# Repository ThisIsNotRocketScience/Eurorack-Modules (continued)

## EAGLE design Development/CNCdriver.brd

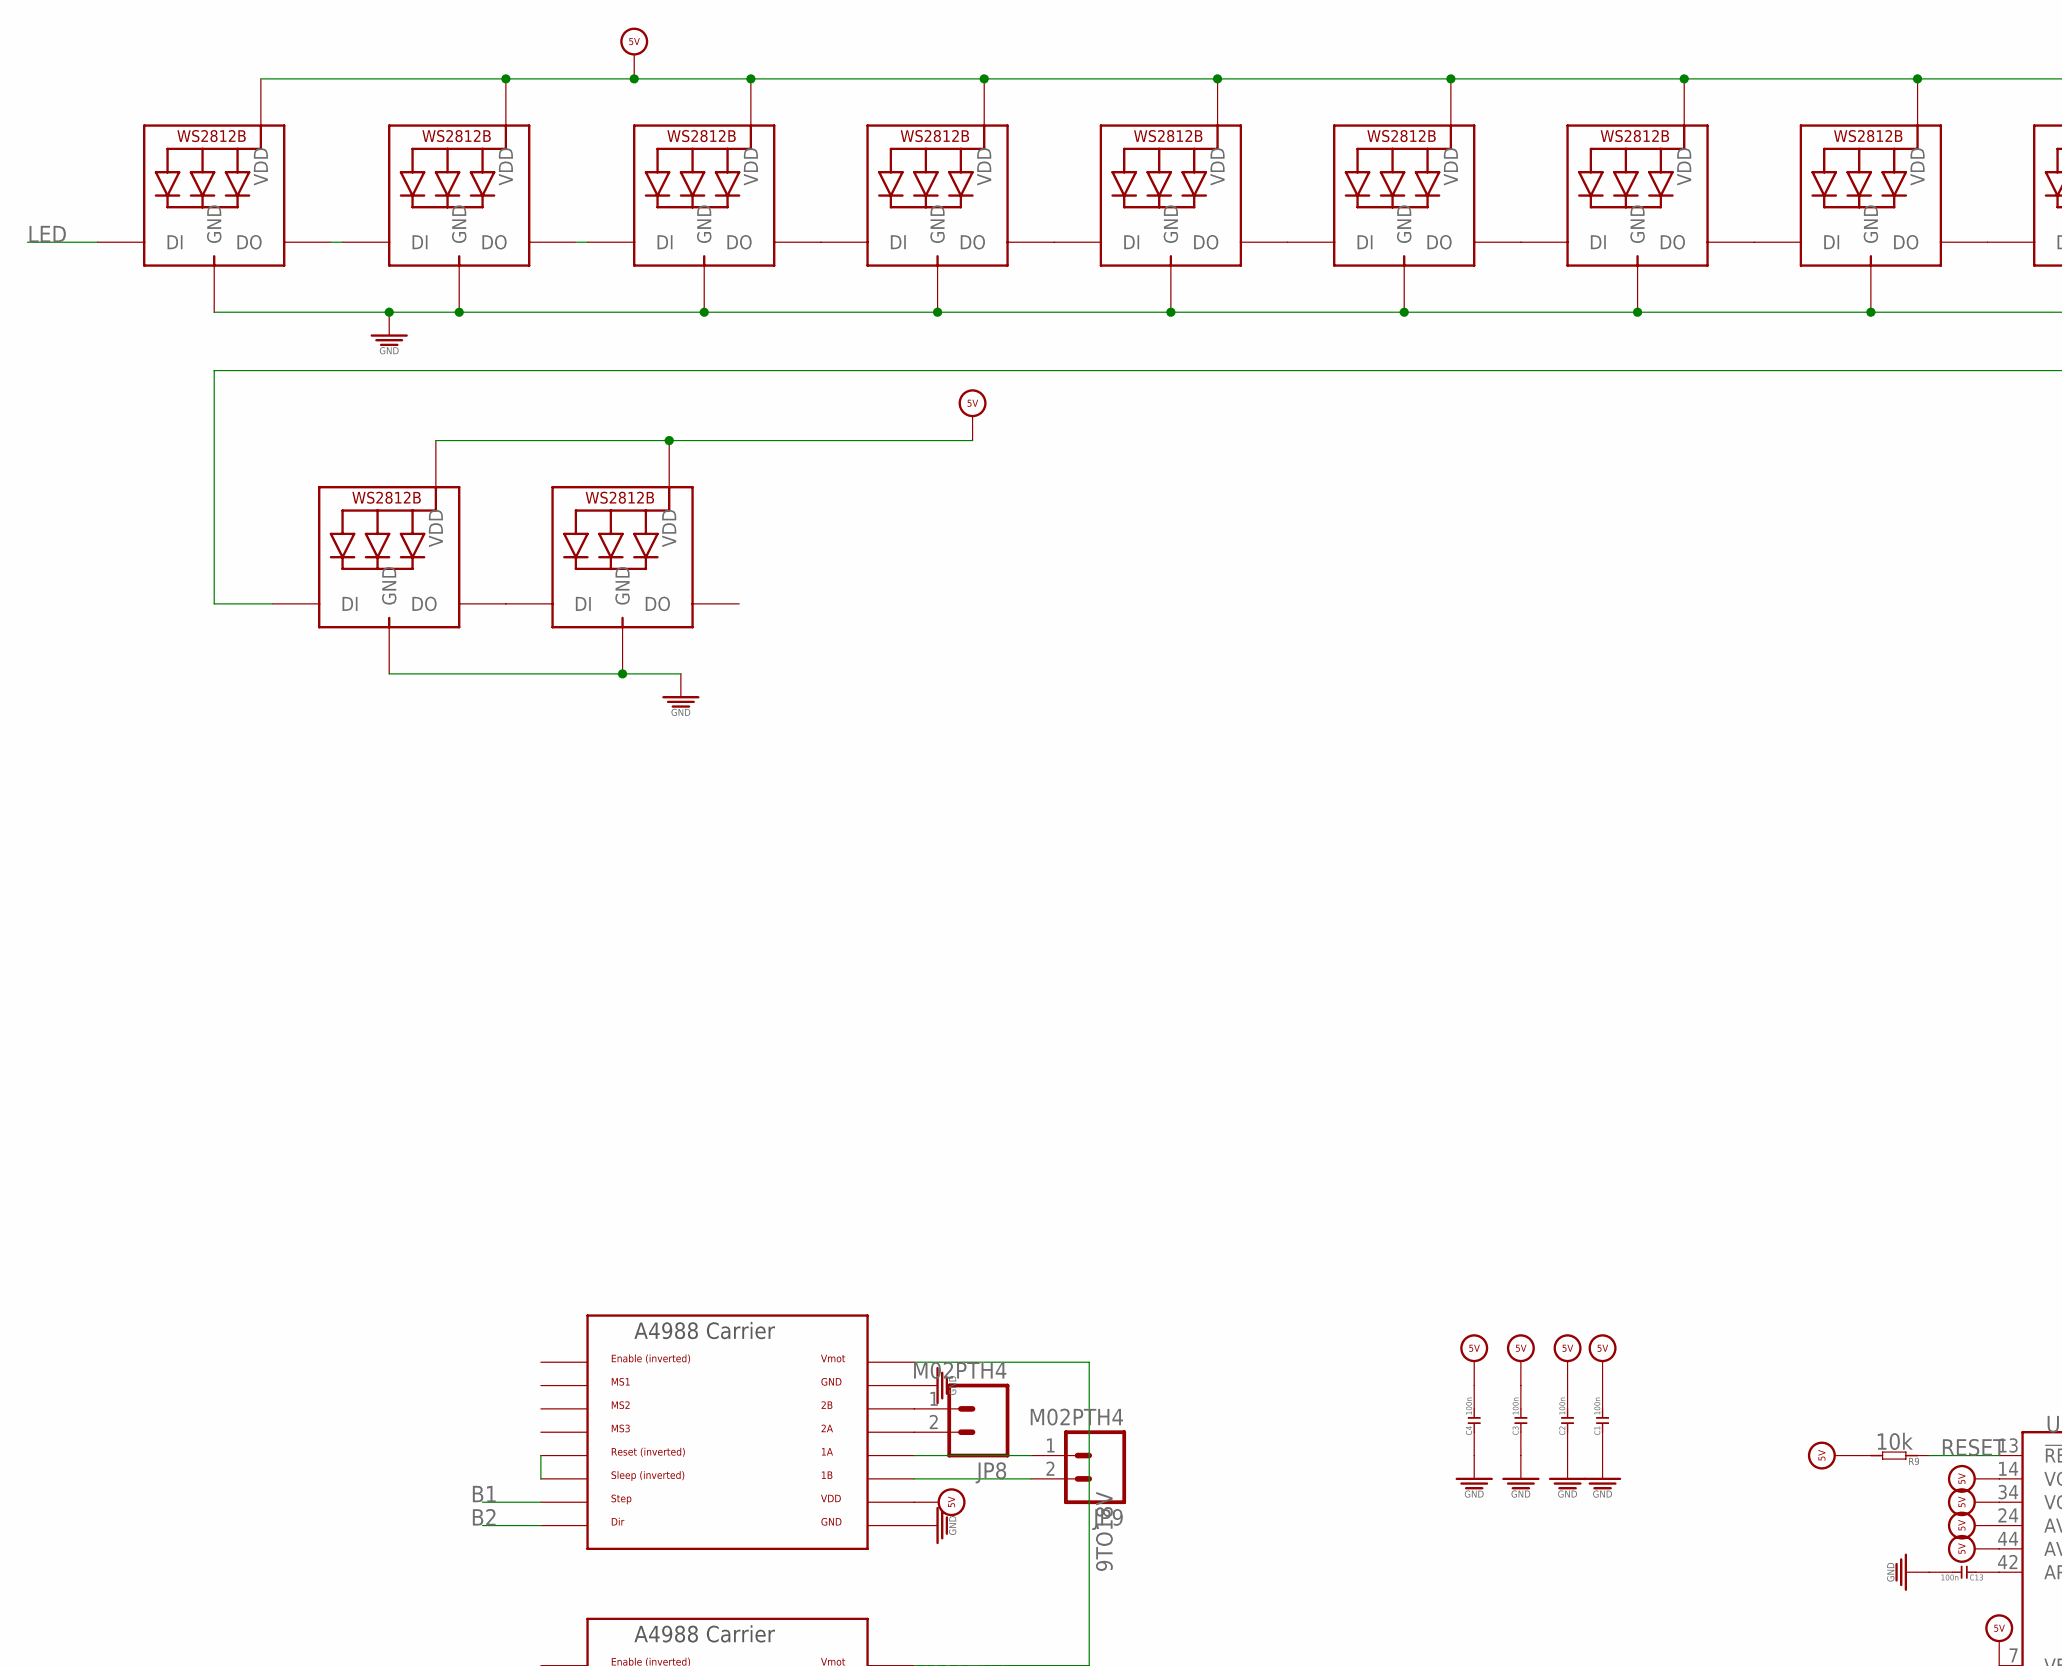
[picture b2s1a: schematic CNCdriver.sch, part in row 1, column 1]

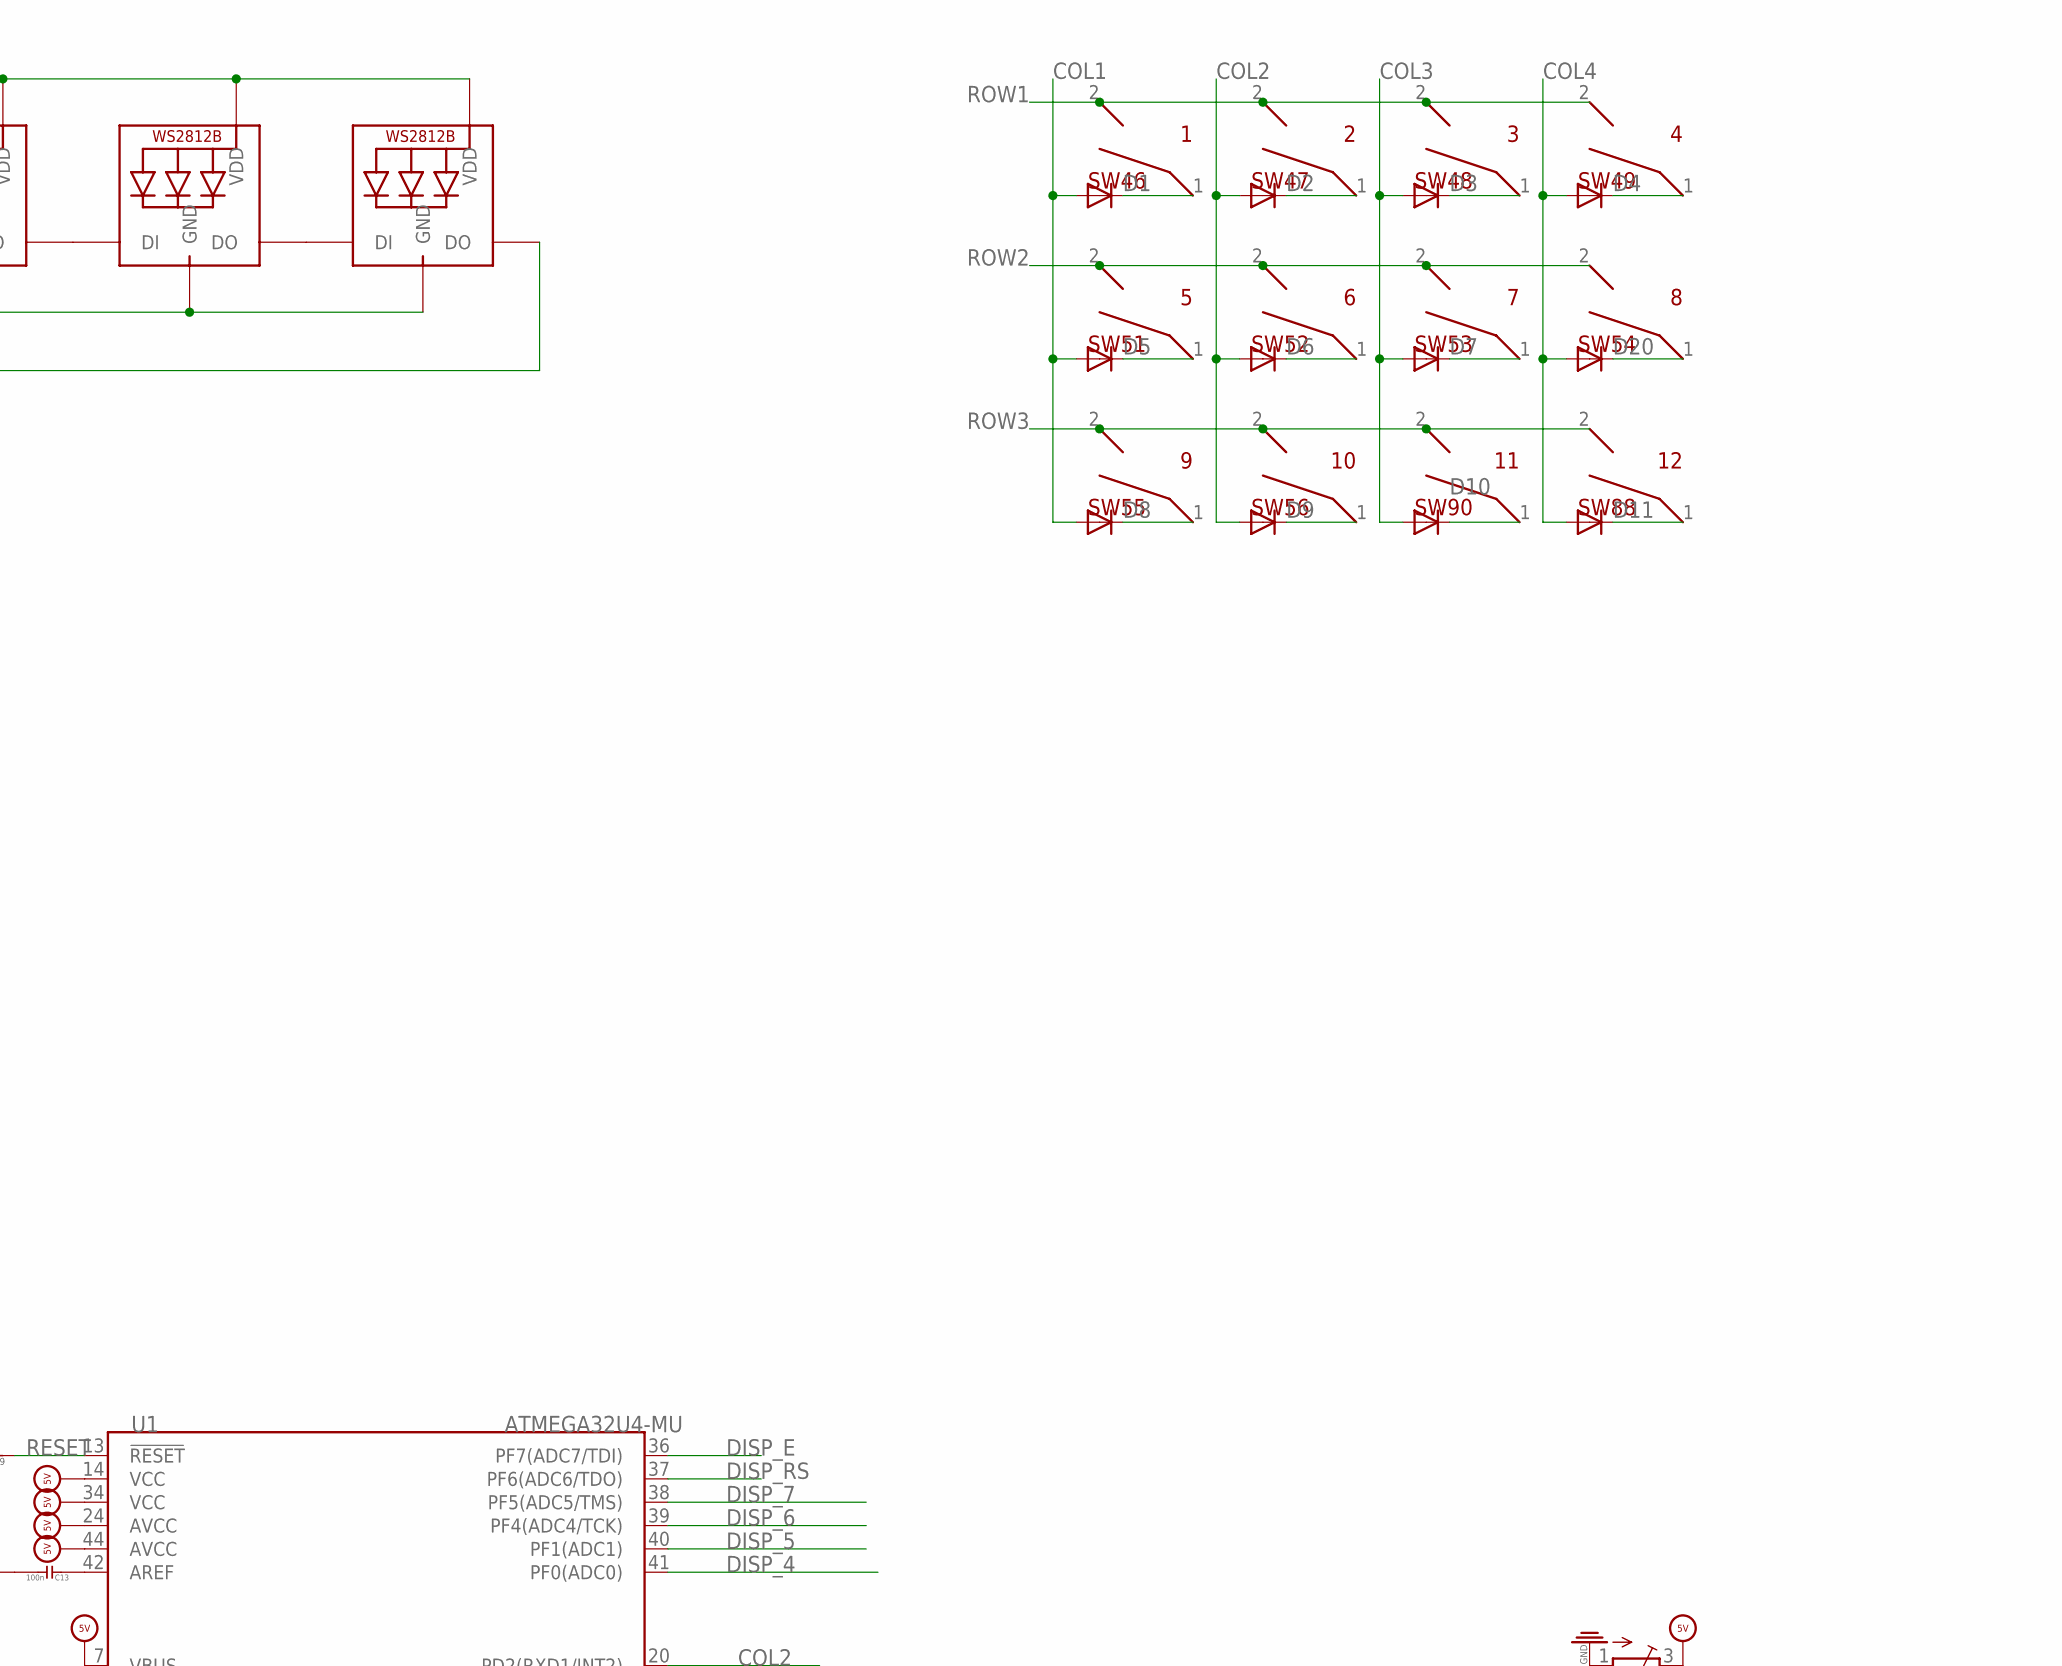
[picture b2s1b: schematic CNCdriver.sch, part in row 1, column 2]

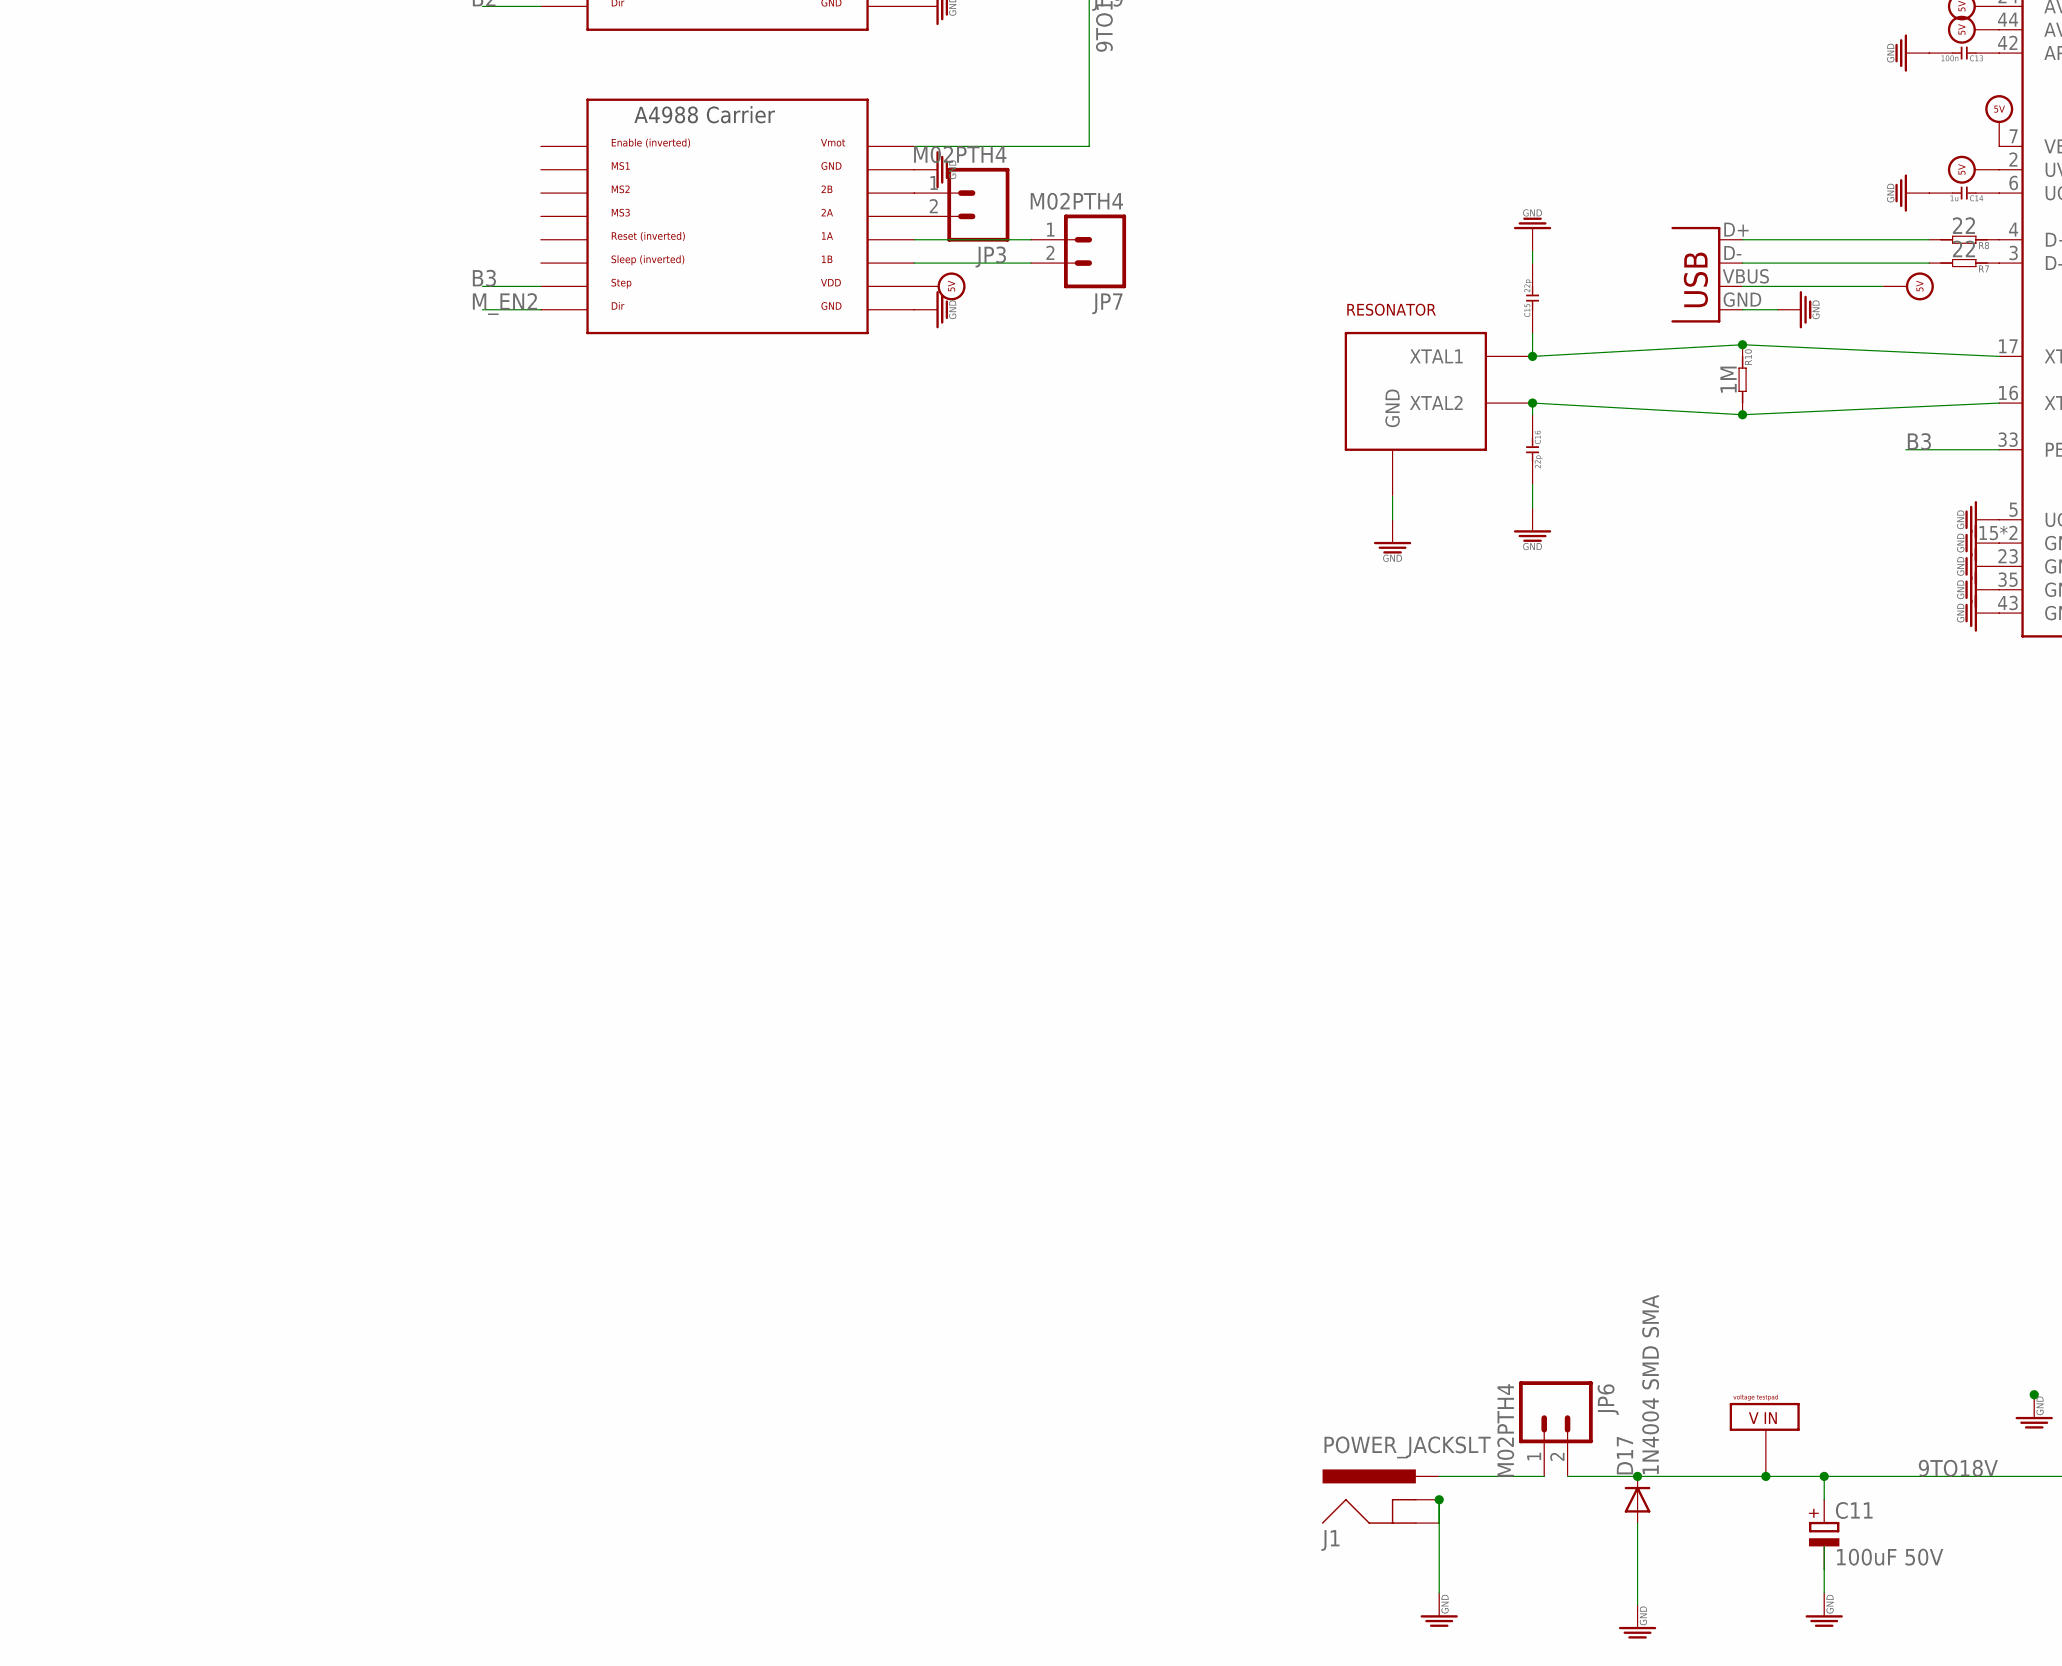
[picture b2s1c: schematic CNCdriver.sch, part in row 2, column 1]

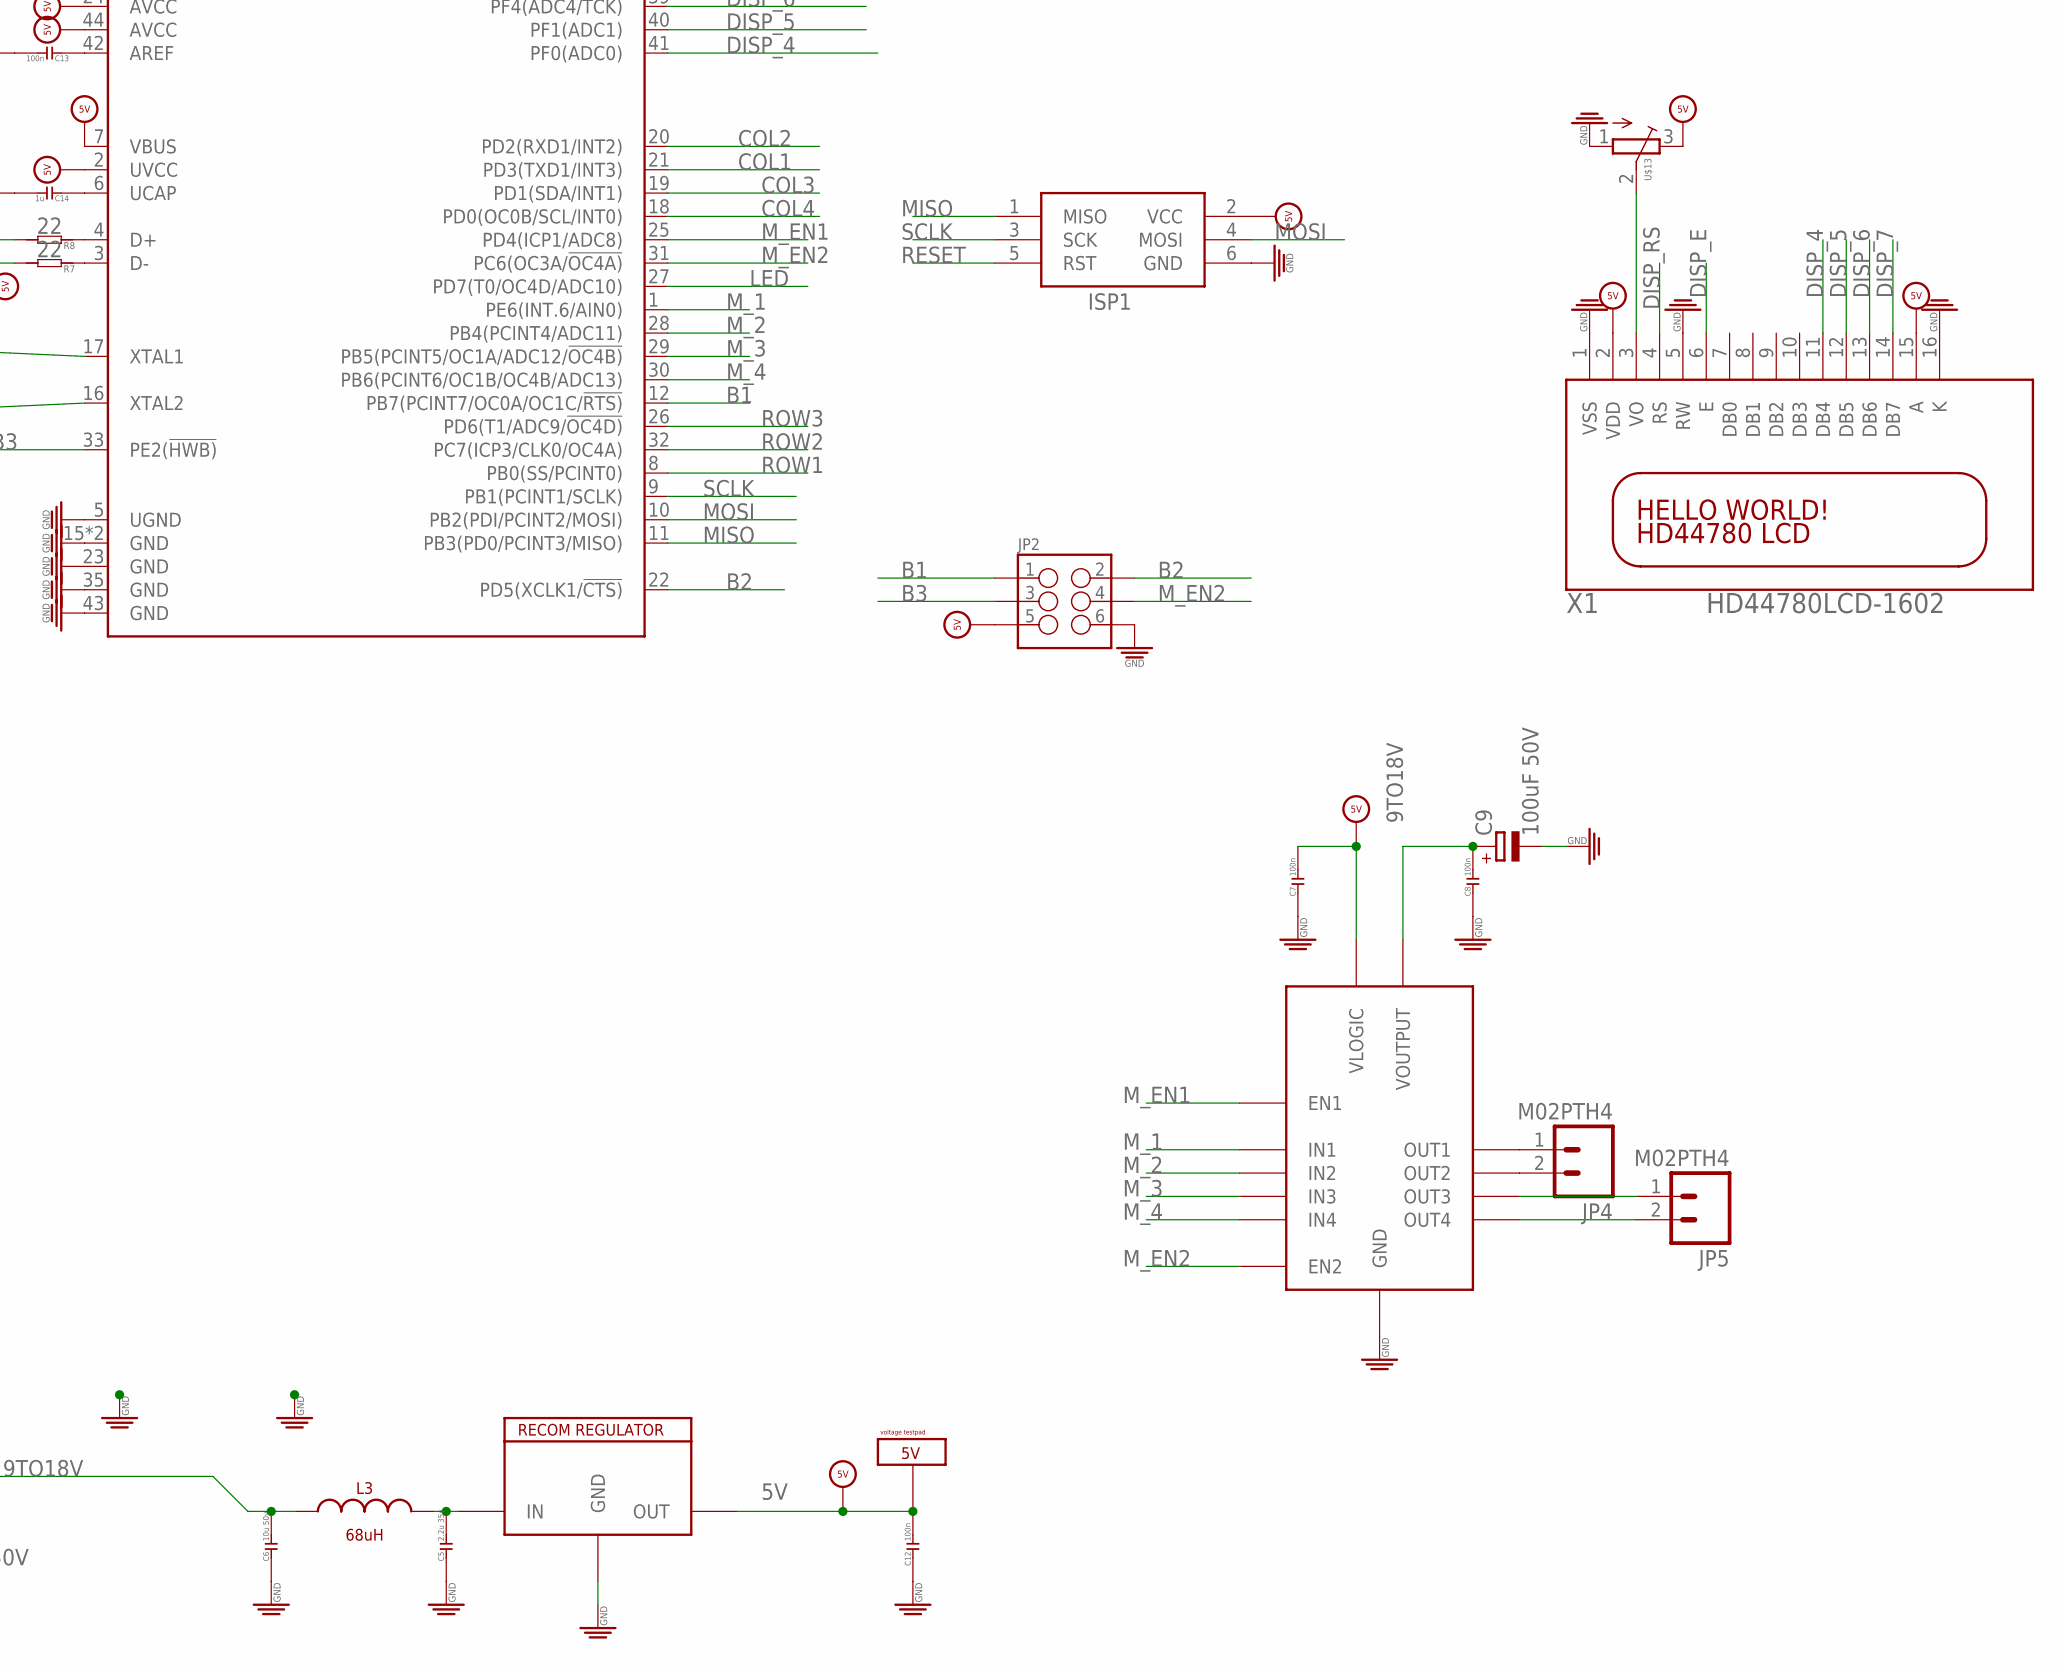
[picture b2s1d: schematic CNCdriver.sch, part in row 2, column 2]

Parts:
C1, C2, C3, C4, C7, C8, C12, C13: 100n; C0603
C5: 2.2u 35v; C0603
C6: 10u 50v; C0603
C9, C11: 100uF 50V; 153CLV-1010
C14: 1u; C0603
C15, C16: 22p; C0603
D1, D2, D3, D4, D5, D6, D7, D8, D9, D10, D11, D20: CGRM4001-G; SOD-123_MINI-SMA
D17: 1N4004 SMD SMA; DO214AC
ISP1: AVRISP-6; AVRISP
J1: POWER_JACKSLT; POWER_JACK_SLOT
JP1: USB-B; USB-B-PTH
JP2: M03X2; 2X3-SHROUDED
JP3, JP4, JP5, JP6, JP7, JP8, JP9: M02PTH4; 1X02_XTRA_BIG
L3: 68uH; SWRB120XS
LED13, LED14, LED15, LED16, LED17, LED18, LED19, LED20, LED21, LED22, LED23, LED24: WS2812B3535; LED3535
R7, R8: 22; R0603
R9: 10k; R0603
R10: 1M; R0603
SW46: 1; MX1A-XXNW
SW47: 2; MX1A-XXNW
SW48: 3; MX1A-XXNW
SW49: 4; MX1A-XXNW
SW51: 5; MX1A-XXNW
SW52: 6; MX1A-XXNW
SW53: 7; MX1A-XXNW
SW54: 8; MX1A-XXNW
SW55: 9; MX1A-XXNW
SW56: 10; MX1A-XXNW
SW88: 12; MX1A-XXNW
SW90: 11; MX1A-XXNW
U1: ATMEGA32U4-MU; QFN44
U$9: L293D; SO20
U$13: TRIMPOTTC33X; TC33X
U$15, U$16: A4983CARRIER; A4988BREAKOUT
U$17: RECOM_REGULATOR; R-78E5.0-1.0
U$25, U$29: VOLTAGETESTPAD; POWERTESTPAD
U$60: RESONATOR; 16MHZXTAL
X1: HD44780LCD-1602; LCD1602

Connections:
9TO18V: C6.2, C8.2, C9.+, C11.+, D17.C, JP6.2, L3.P$1, U$9.P$10 (VOUTPUT), U$15.VMOT, U$16.VMOT, U$29.P$1, U$29.P$2, U$29.P$3
B1: JP2.1, U1.12 (PB7(PCINT7/OC0A/OC1C/!RTS)), U$15.STEP
B2: JP2.2, U1.22 (PD5(XCLK1/!CTS)), U$15.DIR
B3: JP2.3, U1.33 (PE2(!HWB)), U$16.STEP
COL1: D1.A, D5.A, D8.A, U1.21 (PD3(TXD1/INT3))
COL2: D2.A, D6.A, D9.A, U1.20 (PD2(RXD1/INT2))
COL3: D3.A, D7.A, D10.A, U1.19 (PD1(SDA/INT1))
COL4: D4.A, D11.A, D20.A, U1.18 (PD0(OC0B/SCL/INT0))
DISP_4: U1.41 (PF0(ADC0)), X1.11 (DB4)
DISP_5: U1.40 (PF1(ADC1)), X1.12 (DB5)
DISP_6: U1.39 (PF4(ADC4/TCK)), X1.13 (DB6)
DISP_7: U1.38 (PF5(ADC5/TMS)), X1.14 (DB7)
DISP_E: U1.36 (PF7(ADC7/TDI)), X1.6 (E)
DISP_RS: U1.37 (PF6(ADC6/TDO)), X1.4 (RS)
GND: C1.1, C2.1, C3.1, C4.1, C5.1, C6.1, C7.1, C8.1, C9.-, C11.-, C12.1, C13.2, C14.2, C15.2, C16.2, D17.A, ISP1.6 (GND), J1.GND@1 (GNDBREAK), J1.GND@2 (GND), JP1.GND, JP2.6, LED13.3 (GND), LED14.3 (GND), LED15.3 (GND), LED16.3 (GND), LED17.3 (GND), LED18.3 (GND), LED19.3 (GND), LED20.3 (GND), LED21.3 (GND), LED22.3 (GND), LED23.3 (GND), LED24.3 (GND), U1.5 (UGND), U1.15 (GND), U1.23 (GND), U1.35 (GND), U1.43 (GND), U1.TAB (GND), U$9.P$4 (GND), U$9.P$5 (GND), U$9.P$6 (GND), U$9.P$7 (GND), U$9.P$14 (GND), U$9.P$15 (GND), U$9.P$16 (GND), U$9.P$17 (GND), U$13.1 (A), U$15.GND, U$15.GND@0 (GND), U$16.GND, U$16.GND@0 (GND), U$17.P$2 (GND), U$60.P$2 (GND), U$60.P$4 (GND), X1.1 (VSS), X1.5 (RW), X1.16 (K)
LED: LED13.4 (DI), U1.27 (PD7(T0/OC4D/ADC10))
MISO: ISP1.1 (MISO), U1.11 (PB3(PD0/PCINT3/MISO))
MOSI: ISP1.4 (MOSI), U1.10 (PB2(PDI/PCINT2/MOSI))
M_1: U1.1 (PE6(INT.6/AIN0)), U$9.P$2 (IN1)
M_2: U1.28 (PB4(PCINT4/ADC11)), U$9.P$9 (IN2)
M_3: U1.29 (PB5(PCINT5/OC1A/ADC12/!OC4B)), U$9.P$12 (IN3)
M_4: U1.30 (PB6(PCINT6/OC1B/OC4B/ADC13)), U$9.P$19 (IN4)
M_EN1: U1.25 (PD4(ICP1/ADC8)), U$9.P$1 (EN1)
M_EN2: JP2.4, U1.31 (PC6(OC3A/!OC4A)), U$9.P$11 (EN2), U$16.DIR
unnamed: D1.C, SW46.1
unnamed: D2.C, SW47.1
unnamed: D3.C, SW48.1
unnamed: D4.C, SW49.1
unnamed: D5.C, SW51.1
unnamed: D6.C, SW52.1
unnamed: D7.C, SW53.1
unnamed: D8.C, SW55.1
unnamed: D9.C, SW56.1
unnamed: D10.C, SW90.1
unnamed: D11.C, SW88.1
unnamed: U$15.RST, U$15.SLP (SLEEP)
unnamed: JP7.1, U$16.1A
unnamed: JP7.2, U$16.1B
unnamed: JP3.2, U$16.2A
unnamed: JP3.1, U$16.2B
unnamed: JP9.1, U$15.1A
unnamed: JP9.2, U$15.1B
unnamed: JP8.2, U$15.2A
unnamed: D20.C, SW54.1
unnamed: J1.PWR, JP6.1
unnamed: C5.2, L3.P$2, U$17.P$1 (IN)
unnamed: JP8.1, U$15.2B
unnamed: U$13.2 (S), X1.3 (VO)
unnamed: JP4.1, U$9.P$3 (OUT1)
unnamed: JP4.2, U$9.P$8 (OUT2)
unnamed: JP5.1, U$9.P$13 (OUT3)
unnamed: JP5.2, U$9.P$18 (OUT4)
unnamed: LED13.2 (DO), LED14.4 (DI)
unnamed: LED14.2 (DO), LED15.4 (DI)
unnamed: LED15.2 (DO), LED16.4 (DI)
unnamed: LED16.2 (DO), LED17.4 (DI)
unnamed: LED18.2 (DO), LED19.4 (DI)
unnamed: LED19.2 (DO), LED20.4 (DI)
unnamed: LED20.2 (DO), LED21.4 (DI)
unnamed: LED21.2 (DO), LED22.4 (DI)
unnamed: LED17.2 (DO), LED18.4 (DI)
unnamed: LED23.2 (DO), LED24.4 (DI)
unnamed: LED22.2 (DO), LED23.4 (DI)
unnamed: JP1.D-, R7.2
unnamed: JP1.D+, R8.2
unnamed: C13.1, U1.42 (AREF)
unnamed: R8.1, U1.4 (D+)
unnamed: R7.1, U1.3 (D-)
unnamed: C14.1, U1.6 (UCAP)
unnamed: C15.1, R10.1, U1.17 (XTAL1), U$60.P$1 (XTAL1)
unnamed: C16.1, R10.2, U1.16 (XTAL2), U$60.P$3 (XTAL2)
RESET: ISP1.5 (RST), R9.1, U1.13 (!RESET)
ROW1: SW46.2, SW47.2, SW48.2, SW49.2, U1.8 (PB0(SS/PCINT0))
ROW2: SW51.2, SW52.2, SW53.2, SW54.2, U1.32 (PC7(ICP3/CLK0/OC4A))
ROW3: SW55.2, SW56.2, SW88.2, SW90.2, U1.26 (PD6(T1/ADC9/!OC4D))
SCLK: ISP1.3 (SCK), U1.9 (PB1(PCINT1/SCLK))

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
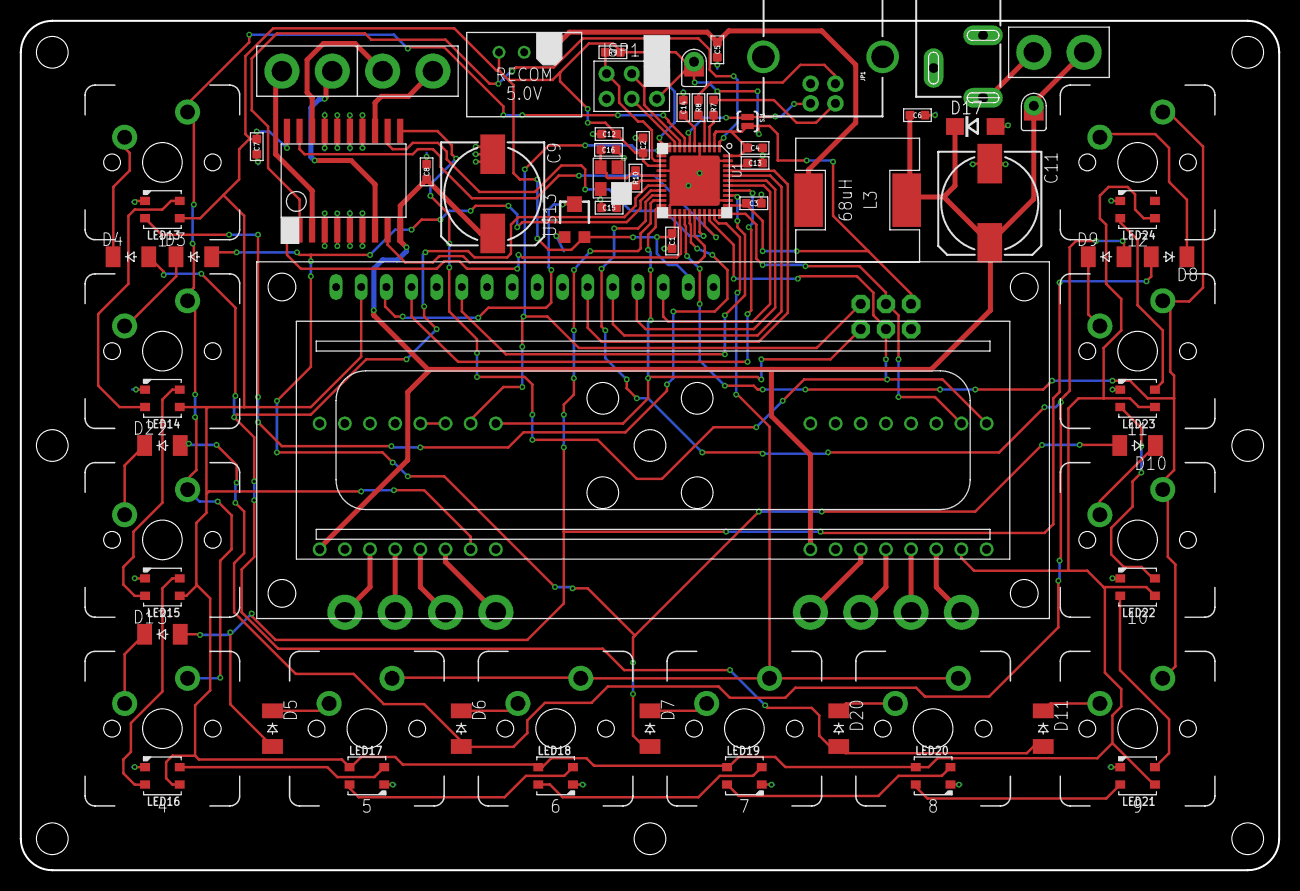
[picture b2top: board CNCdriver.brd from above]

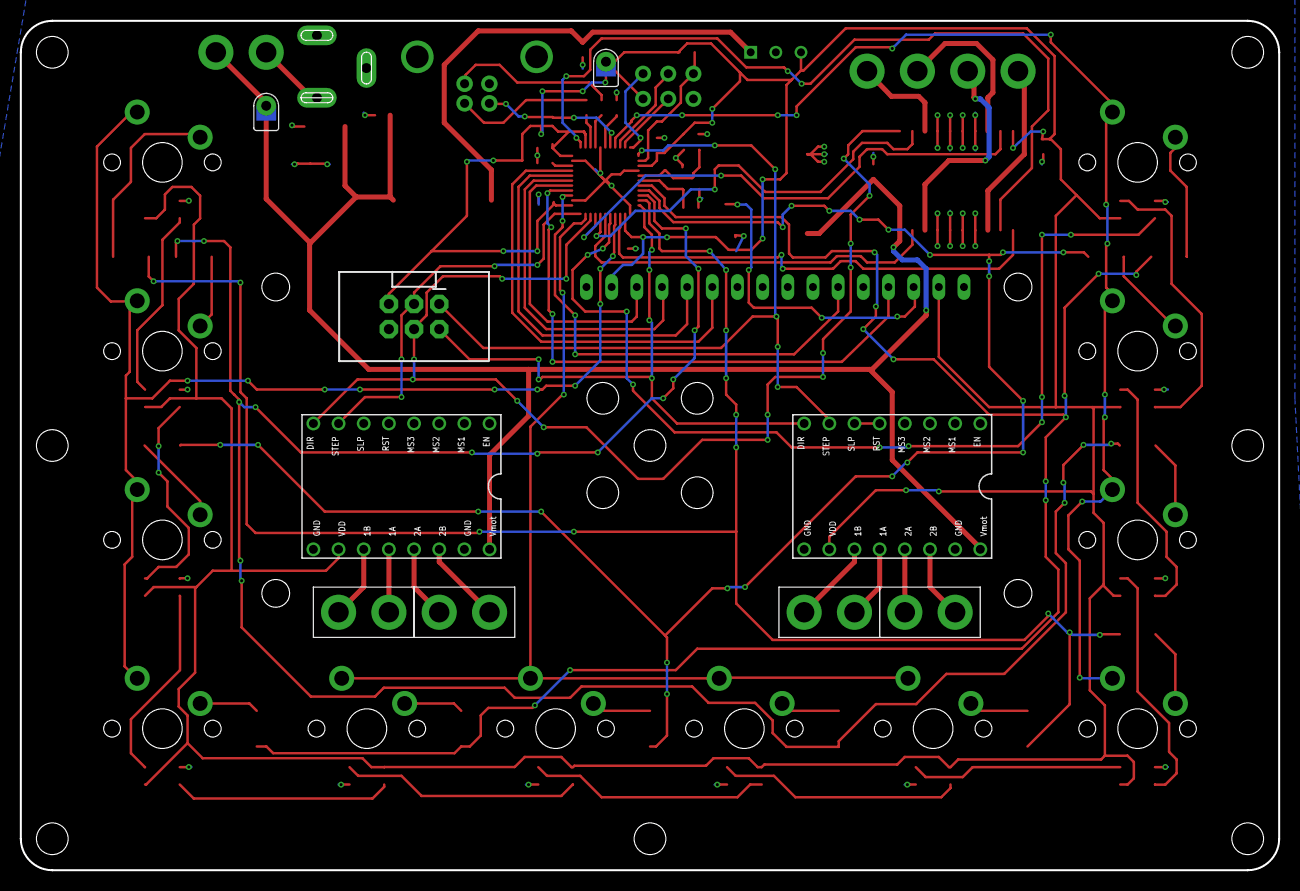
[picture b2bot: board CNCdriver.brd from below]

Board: 2 copper layers, 127.0 x 85.7 mm, 79 parts (7 on the bottom side), 78 nets.

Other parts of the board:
SJ1: SOLDERJUMPERNO; SJ_2S-NO

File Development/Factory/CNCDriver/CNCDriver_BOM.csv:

Comment,Designator,Footprint,LCSC Part #,combinedname,name
CGRM4001-G,"D1, D10, D11, D2, D20, D3, D4, D5, D6, D7, D8, D9",SOD-123_MINI-SMA,,CGRM400*-G_SOD-123_MINI-SMA_CGRM4001-G,CGRM400*-G
4,"SW46",MX1A-XXNW,,CHERRY_MX_MX1A-XXNW_4,CHERRY_MX
3,"SW47",MX1A-XXNW,,CHERRY_MX_MX1A-XXNW_3,CHERRY_MX
2,"SW48",MX1A-XXNW,,CHERRY_MX_MX1A-XXNW_2,CHERRY_MX
1,"SW49",MX1A-XXNW,,CHERRY_MX_MX1A-XXNW_1,CHERRY_MX
5,"SW51",MX1A-XXNW,,CHERRY_MX_MX1A-XXNW_5,CHERRY_MX
6,"SW52",MX1A-XXNW,,CHERRY_MX_MX1A-XXNW_6,CHERRY_MX
7,"SW53",MX1A-XXNW,,CHERRY_MX_MX1A-XXNW_7,CHERRY_MX
8,"SW54",MX1A-XXNW,,CHERRY_MX_MX1A-XXNW_8,CHERRY_MX
12,"SW55",MX1A-XXNW,,CHERRY_MX_MX1A-XXNW_12,CHERRY_MX
11,"SW56",MX1A-XXNW,,CHERRY_MX_MX1A-XXNW_11,CHERRY_MX
9,"SW88",MX1A-XXNW,,CHERRY_MX_MX1A-XXNW_9,CHERRY_MX
10,"SW90",MX1A-XXNW,,CHERRY_MX_MX1A-XXNW_10,CHERRY_MX
WS2812B3535,"LED13, LED14, LED15, LED16, LED17, LED18, LED19, LED20, LED21, LED22, LED23, LED24",LED3535,,WS2812B_LED3535_WS2812B3535,WS2812B
ATMEGA32U4-MU,"U1",QFN44,,ATMEGA32U4_QFN44_ATMEGA32U4-MU,ATMEGA32U4
USB-B,"JP1",USB-B-PTH,,USB_USB-B-PTH_USB-B,USB
22,"R7, R8",R0603,,R*_R0603_22,R*
10k,"R9",R0603,,R*_R0603_10k,R*
1M,"R10",R0603,,R*_R0603_1M,R*
100n,"C13, C1, C2, C3, C4, C12, C7, C8",C0603,,C*_C0603_100n,C*
1u,"C14",C0603,,C*_C0603_1u,C*
22p,"C15, C16",C0603,,C*_C0603_22p,C*
2.2u 35v,"C5",C0603,,C*_C0603_2.2u_35v,C*
10u 50v,"C6",C0603,,C*_C0603_10u_50v,C*
AVRISP-6,"ISP1",AVRISP,,AVRISP_AVRISP_AVRISP-6,AVRISP
RESONATOR,"U$60",16MHZXTAL,,RESONATOR_16MHZXTAL_RESONATOR,RESONATOR
,"JP2",2X3-SHROUDED,,M03X2_2X3-SHROUDED_,M03X2
HD44780LCD-1602,"X1",LCD1602,,HD44780LCD_LCD1602_HD44780LCD-1602,HD44780LCD
L293D,"U$9",SO20,,L293D_SO20_L293D,L293D
POWER_JACKSLT,"J1",POWER_JACK_SLOT,,POWER_JACK_POWER_JACK_SLOT_POWER_JACKSLT,POWER_JACK
M02PTH4,"JP6, JP4, JP5, JP3, JP7, JP8, JP9",1X02_XTRA_BIG,,M02_1X02_XTRA_BIG_M02PTH4,M02
100uF 50V,"C11, C9",153CLV-1010,,CPOL-EU_153CLV-1010_100uF_50V,CPOL-EU
RECOM_REGULATOR,"U$17",R-78E5.0-1.0,,RECOM_REGULATOR_R-78E5.0-1.0_RECOM_REGULATOR,RECOM_REGULATOR
1N4004 SMD SMA,"D17",DO214AC,,DIODE-_DO214AC_1N4004_SMD_SMA,DIODE-
VOLTAGETESTPAD,"U$25, U$29",POWERTESTPAD,,VOLTAGETESTPAD_POWERTESTPAD_VOLTAGETESTPAD,VOLTAGETESTPAD
68uH,"L3",SWRB120XS,,L_SWRB120XS_68uH,L
,"U$13",TC33X,,TRIMPOT_TC33X_,TRIMPOT
A4983CARRIER,"U$15, U$16",A4988BREAKOUT,,A4983CARRIER_A4988BREAKOUT_A4983CARRIER,A4983CARRIER
SOLDERJUMPERNO,"SJ1",SJ_2S-NO,,SOLDERJUMPER_SJ_2S-NO_SOLDERJUMPERNO,SOLDERJUMPER
